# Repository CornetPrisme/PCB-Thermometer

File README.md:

# ESP32-C6 Temperature and humidity sensors

Custom environmental sensor node based on the ESP32-C6 (Wi-Fi 6, BLE 5, Zigbee/Thread). It features three distinct temperature and humidity sensors on a shared I2C bus, is powered via USB-C (3.3V LDO), and includes two external 3-pin headers for hardware expansion.

## IC List

- ESP32-C6 (MCU)
- HDC2080 (humidity & temperature sensor)
- TMP102 (temperature sensor)
- LM75 (temperature sensor)
- TLV75733PDBVR (LDO)

## Top preview

## Preview 3d render

```c
// Shared I2C bus (Sensors)
#define I2C_SCL_PIN GPIO7
#define I2C_SDA_PIN GPIO6

// Expansion connectors (External 3-pin headers)
#define EXT_HEADER_1_PIN GPIO2
#define EXT_HEADER_2_PIN GPIO3

// Hardware sensor interrupts
#define DRDY_PIN GPIO20   // HDC2080 interrupt
#define ALERT_PIN GPIO19  // TMP102 alert
#define OS_PIN GPIO18     // LM75 thermal alarm
```

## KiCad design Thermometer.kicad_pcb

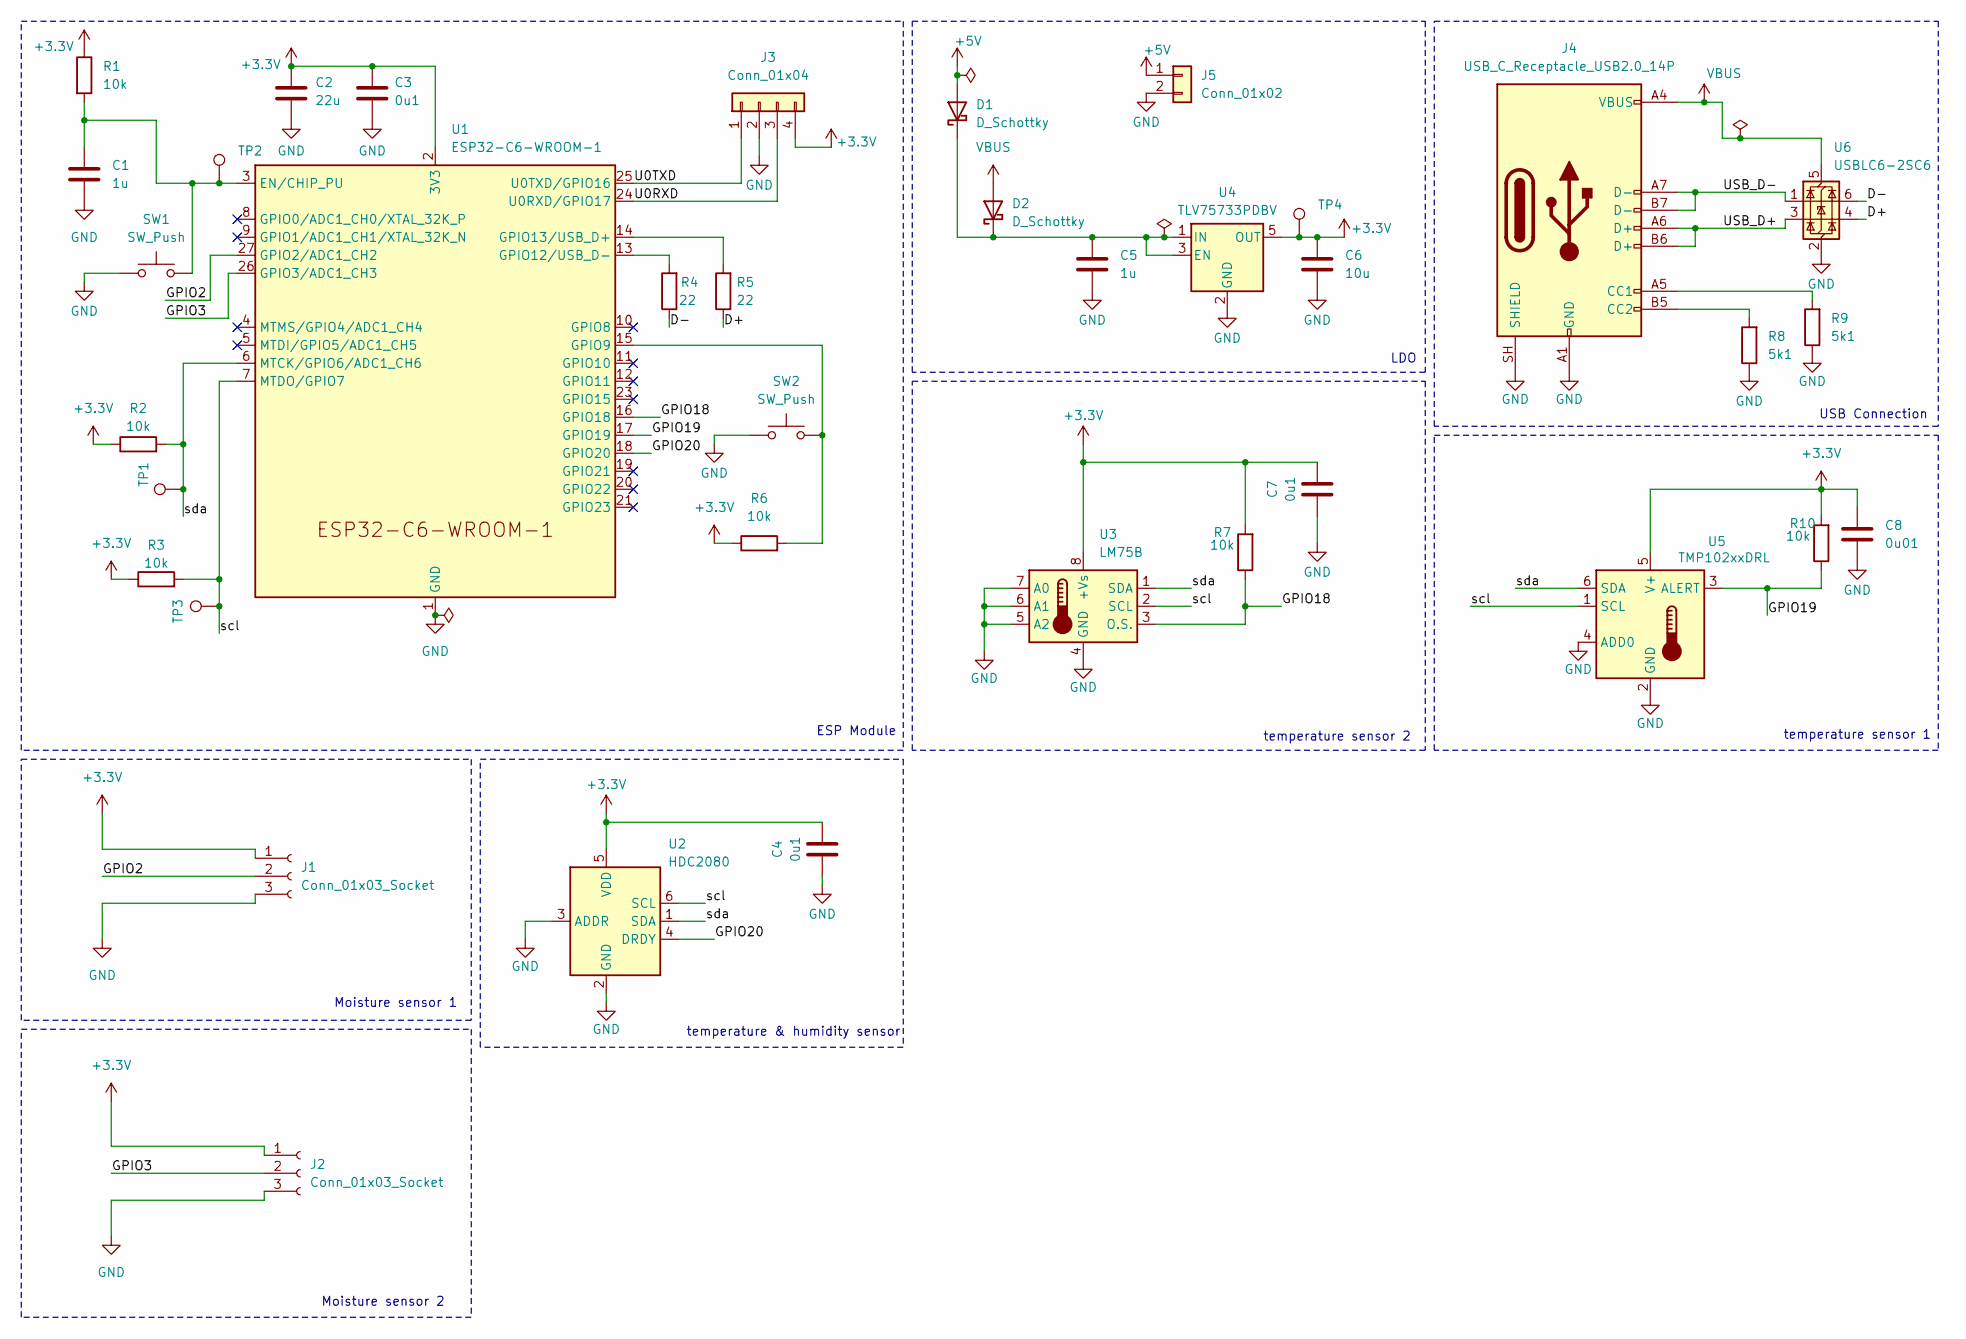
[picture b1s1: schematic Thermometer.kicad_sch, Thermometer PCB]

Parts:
C1, C5: 1u; C_0603_1608Metric; Manufacturer Part Number CL10A105KB8NNNC; JLCPCB Part # C15849
C2: 22u; C_1206_3216Metric; Manufacturer Part Number CL31A226KAHNNNE; JLCPCB Part # C12891
C3, C4, C7: 0u1; C_0603_1608Metric; Manufacturer Part Number CC0603KRX7R9BB104; JLCPCB Part # C14663
C6: 10u; C_0603_1608Metric; Manufacturer Part Number CL10A106KP8NNNC; JLCPCB Part # C19702
C8: 0u01; C_0603_1608Metric; Manufacturer Part Number 0603B103K500NT; JLCPCB Part # C57112
D1, D2: D_Schottky; D_SMA; Manufacturer Part Number SS54; JLCPCB Part # C22452
J1, J2: Conn_01x03_Socket; JST_XH_B3B-XH-A_1x03_P2.50mm_Vertical
J3: Conn_01x04; PinHeader_1x04_P2.54mm_Vertical
J4: USB_C_Receptacle_USB2.0_14P; USB_C_Receptacle_HRO_TYPE-C-31-M-12; Manufacturer Part Number TYPE-C16PIN; JLCPCB Part # C393939
J5: Conn_01x02; JST_XH_B2B-XH-A_1x02_P2.50mm_Vertical
R1, R2, R3, R6, R7, R10: 10k; R_0603_1608Metric; Manufacturer Part Number 0603WAF1002T5E; JLCPCB Part # C25804
R4, R5: 22; R_0603_1608Metric; Manufacturer Part Number 0603WAF220JT5E; JLCPCB Part # C23345
R8, R9: 5k1; R_0603_1608Metric; Manufacturer Part Number 0603WAF5101T5E; JLCPCB Part # C23186
SW1, SW2: SW_Push; SW_SPST_TS-1088-xR025; Manufacturer Part Number TS-1088-AR02016; JLCPCB Part # C720477
TP1, TP2, TP3, TP4: TestPoint; TestPoint_Pad_D3.0mm
U1: ESP32-C6-WROOM-1; Manufacturer Part Number ESP32-C6-WROOM-1-N8; JLCPCB Part # C5366877
U2: HDC2080; Texas_S-PWSON-N6-HDC2080; Manufacturer Part Number HDC2080DMBR; JLCPCB Part # C918141
U3: LM75B; SSOP-8_3.9x5.05mm_P1.27mm; Manufacturer Part Number LM75BD(UMW); JLCPCB Part # C725792
U4: TLV75733PDBV; SOT-23-5; Manufacturer Part Number TLV75733PDBVR; JLCPCB Part # C485517
U5: TMP102xxDRL; SOT-563; Manufacturer Part Number TMP102AIDRLR; JLCPCB Part # C99269
U6: USBLC6-2SC6; SOT-23-6; Manufacturer Part Number USBLC6-2SC6; JLCPCB Part # C7519

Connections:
+3.3V: C2.1, C3.1, C4.2, C6.1, C7.2, C8.1, J1.1, J2.1, J3.4, R1.1, R2.1, R3.1, R6.1, R7.2, R10.2, TP4.1 (1_1), U1.2 (3V3), U2.5 (VDD), U3.8 (+Vs), U4.5 (OUT), U5.5 (V+)
+5V: D1.2 (A), J5.1
/D+: R5.1, U6.4 (I/O2)
/D-: R4.1, U6.6 (I/O1)
/GPIO2: J1.2, U1.27 (GPIO2/ADC1_CH2)
/GPIO3: J2.2, U1.26 (GPIO3/ADC1_CH3)
/GPIO18: R7.1, U1.16 (GPIO18), U3.3 (O.S.)
/GPIO19: R10.1, U1.17 (GPIO19), U5.3 (ALERT)
/GPIO20: U1.18 (GPIO20), U2.4 (DRDY)
/U0RXD: J3.3, U1.24 (U0RXD/GPIO17)
/U0TXD: J3.1, U1.25 (U0TXD/GPIO16)
/USB_D+: J4.A6 (D+), J4.B6 (D+), U6.3 (I/O2)
/USB_D-: J4.A7 (D-), J4.B7 (D-), U6.1 (I/O1)
/scl: R3.2, TP3.1 (1_1), U1.7 (MTDO/GPIO7), U2.6 (SCL), U3.2 (SCL), U5.1 (SCL)
/sda: R2.2, TP1.1 (1_1), U1.6 (MTCK/GPIO6/ADC1_CH6), U2.1 (SDA), U3.1 (SDA), U5.6 (SDA)
GND: C1.2, C2.2, C3.2, C4.1, C5.2, C6.2, C7.1, C8.2, J1.3, J2.3, J3.2, J4.A1 (GND), J4.A12 (GND), J4.B1 (GND), J4.B12 (GND), J4.SH (SHIELD), J5.2, R8.1, R9.1, SW1.1, SW2.1, U1.1 (GND), U1.28 (GND), U1.29 (GND), U2.2 (GND), U2.3 (ADDR), U3.4 (GND), U3.5 (A2), U3.6 (A1), U3.7 (A0), U4.2 (GND), U5.2 (GND), U5.4 (ADD0), U6.2 (GND)
unnamed: C5.1, D1.1 (K), D2.1 (K), U4.1 (IN), U4.3 (EN)
unnamed: J4.A5 (CC1), R9.2
unnamed: J4.B5 (CC2), R8.2
unnamed: C1.1, R1.2, SW1.2, TP2.1 (1_1), U1.3 (EN/CHIP_PU)
unnamed: R6.2, SW2.2, U1.15 (GPIO9)
unnamed: R4.2, U1.13 (GPIO12/USB_D-)
unnamed: R5.2, U1.14 (GPIO13/USB_D+)
VBUS: D2.2 (A), J4.A4 (VBUS), J4.A9 (VBUS), J4.B4 (VBUS), J4.B9 (VBUS), U6.5 (VBUS)

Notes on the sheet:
Moisture sensor 1
USB Connection
temperature & humidity sensor
ESP Module
Moisture sensor 2
temperature sensor 1
temperature sensor 2
LDO

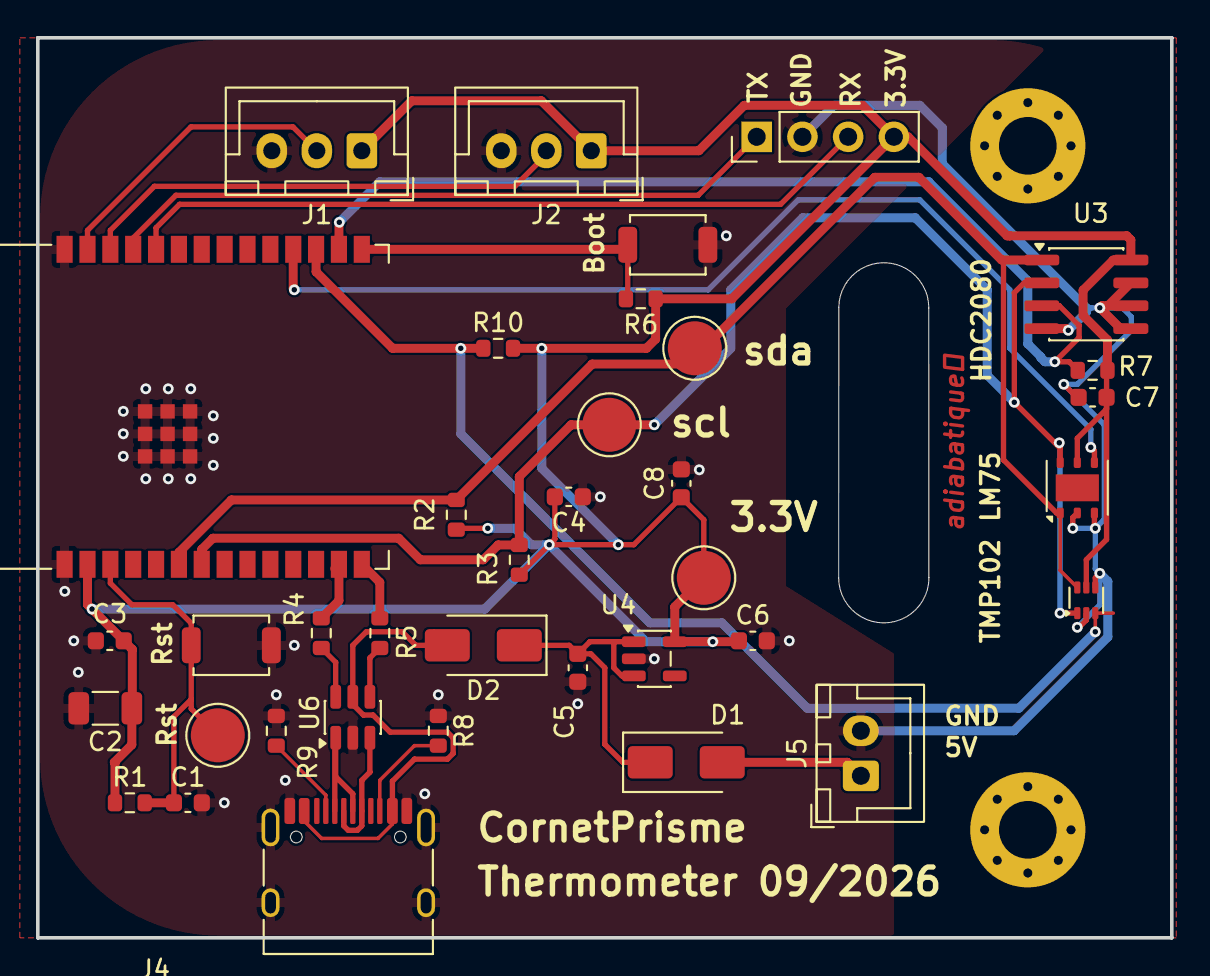
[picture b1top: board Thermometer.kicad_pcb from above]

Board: 2 copper layers, 63.0 x 50.0 mm, 37 parts (0 on the bottom side), 24 nets.

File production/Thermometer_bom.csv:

Designator,Footprint,Quantity,Value,LCSC Part #
"C1, C5",0603,2,1u,C15849
C2,1206,1,22u,C12891
"C3, C4, C7",0603,3,0u1,C14663
C6,0603,1,10u,C19702
C8,0603,1,0u01,C57112
"D1, D2",D_SMA,2,D_Schottky,C22452
"J1, J2",JST_XH_B3B-XH-A_1x03_P2.50mm_Vertical,2,Conn_01x03_Socket,
J4,USB_C_Receptacle_HRO_TYPE-C-31-M-12,1,USB_C_Receptacle_USB2.0_14P,C393939
J5,JST_XH_B2B-XH-A_1x02_P2.50mm_Vertical,1,Conn_01x02,
"R1, R10, R2, R3, R6, R7",0603,6,10k,C25804
"R4, R5",0603,2,22,C23345
"R8, R9",0603,2,5k1,C23186
"SW1, SW2",SW_SPST_TS-1088-xR025,2,SW_Push,C720477
U1,ESP32-C6-WROOM-1,1,ESP32-C6-WROOM-1,C5366877
U2,Texas_S-PWSON-N6-HDC2080,1,HDC2080,C918141
U3,SOIC-8_3.9x4.9mm_P1.27mm,1,LM75B,C725792
U4,SOT-23-5,1,TLV75733PDBV,C485517
U5,SOT-563,1,TMP102xxDRL,C99269
U6,SOT-23-6,1,USBLC6-2SC6,C7519
